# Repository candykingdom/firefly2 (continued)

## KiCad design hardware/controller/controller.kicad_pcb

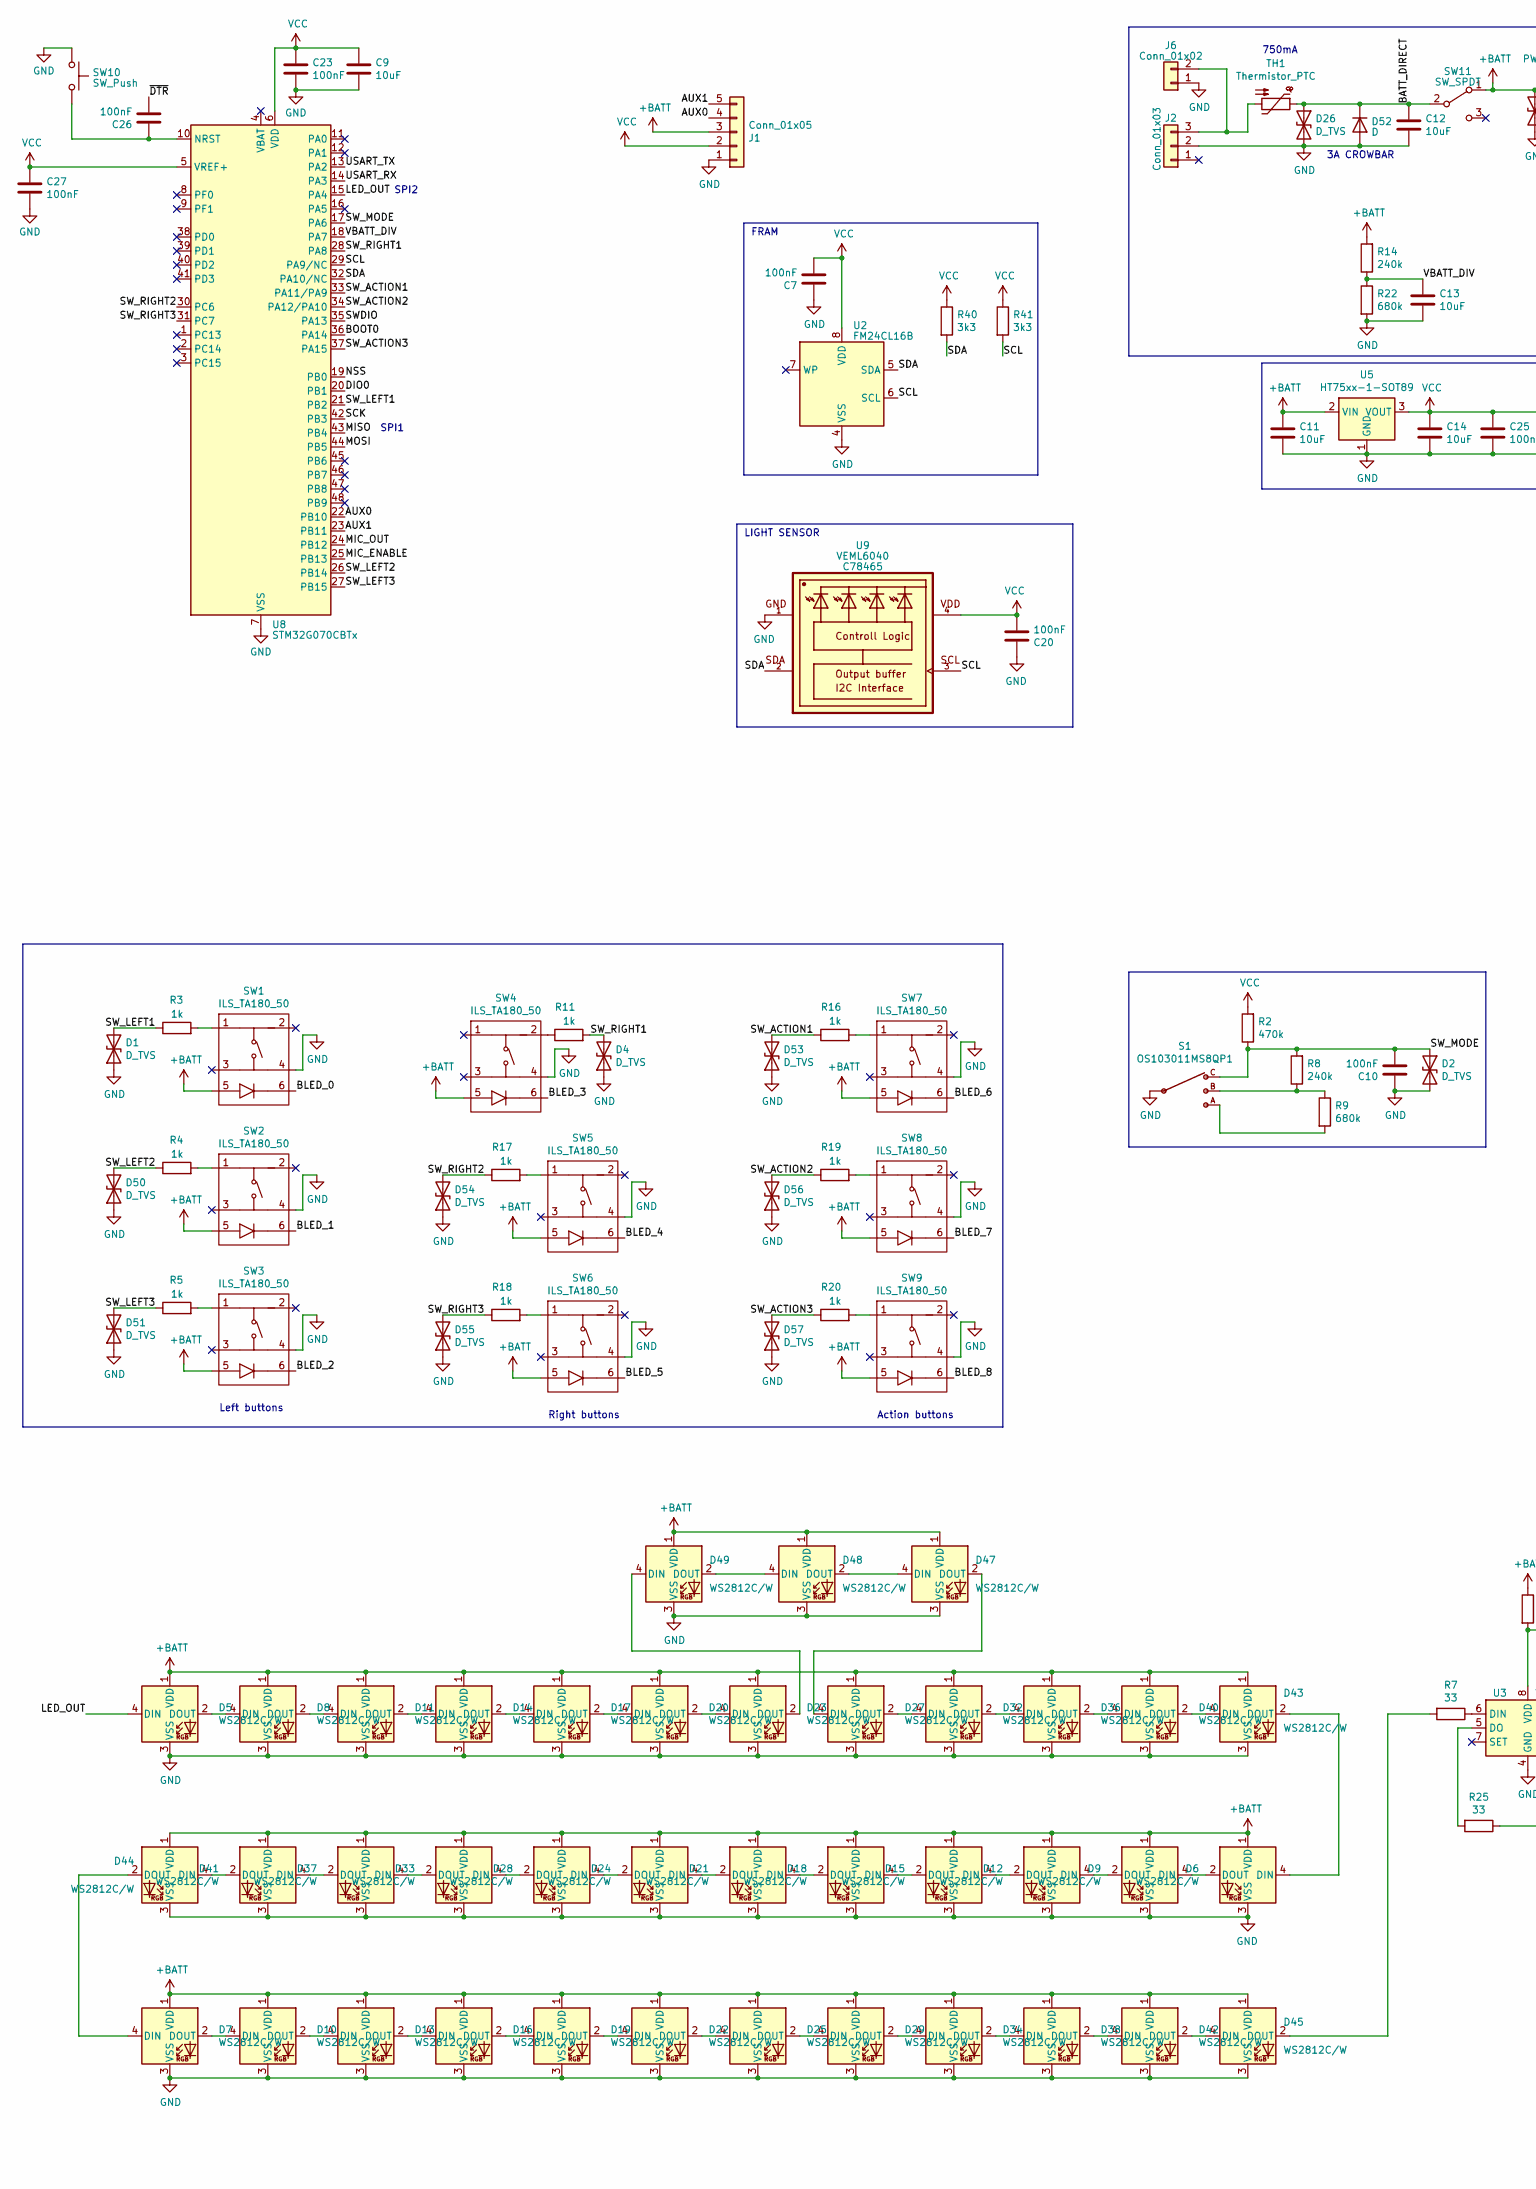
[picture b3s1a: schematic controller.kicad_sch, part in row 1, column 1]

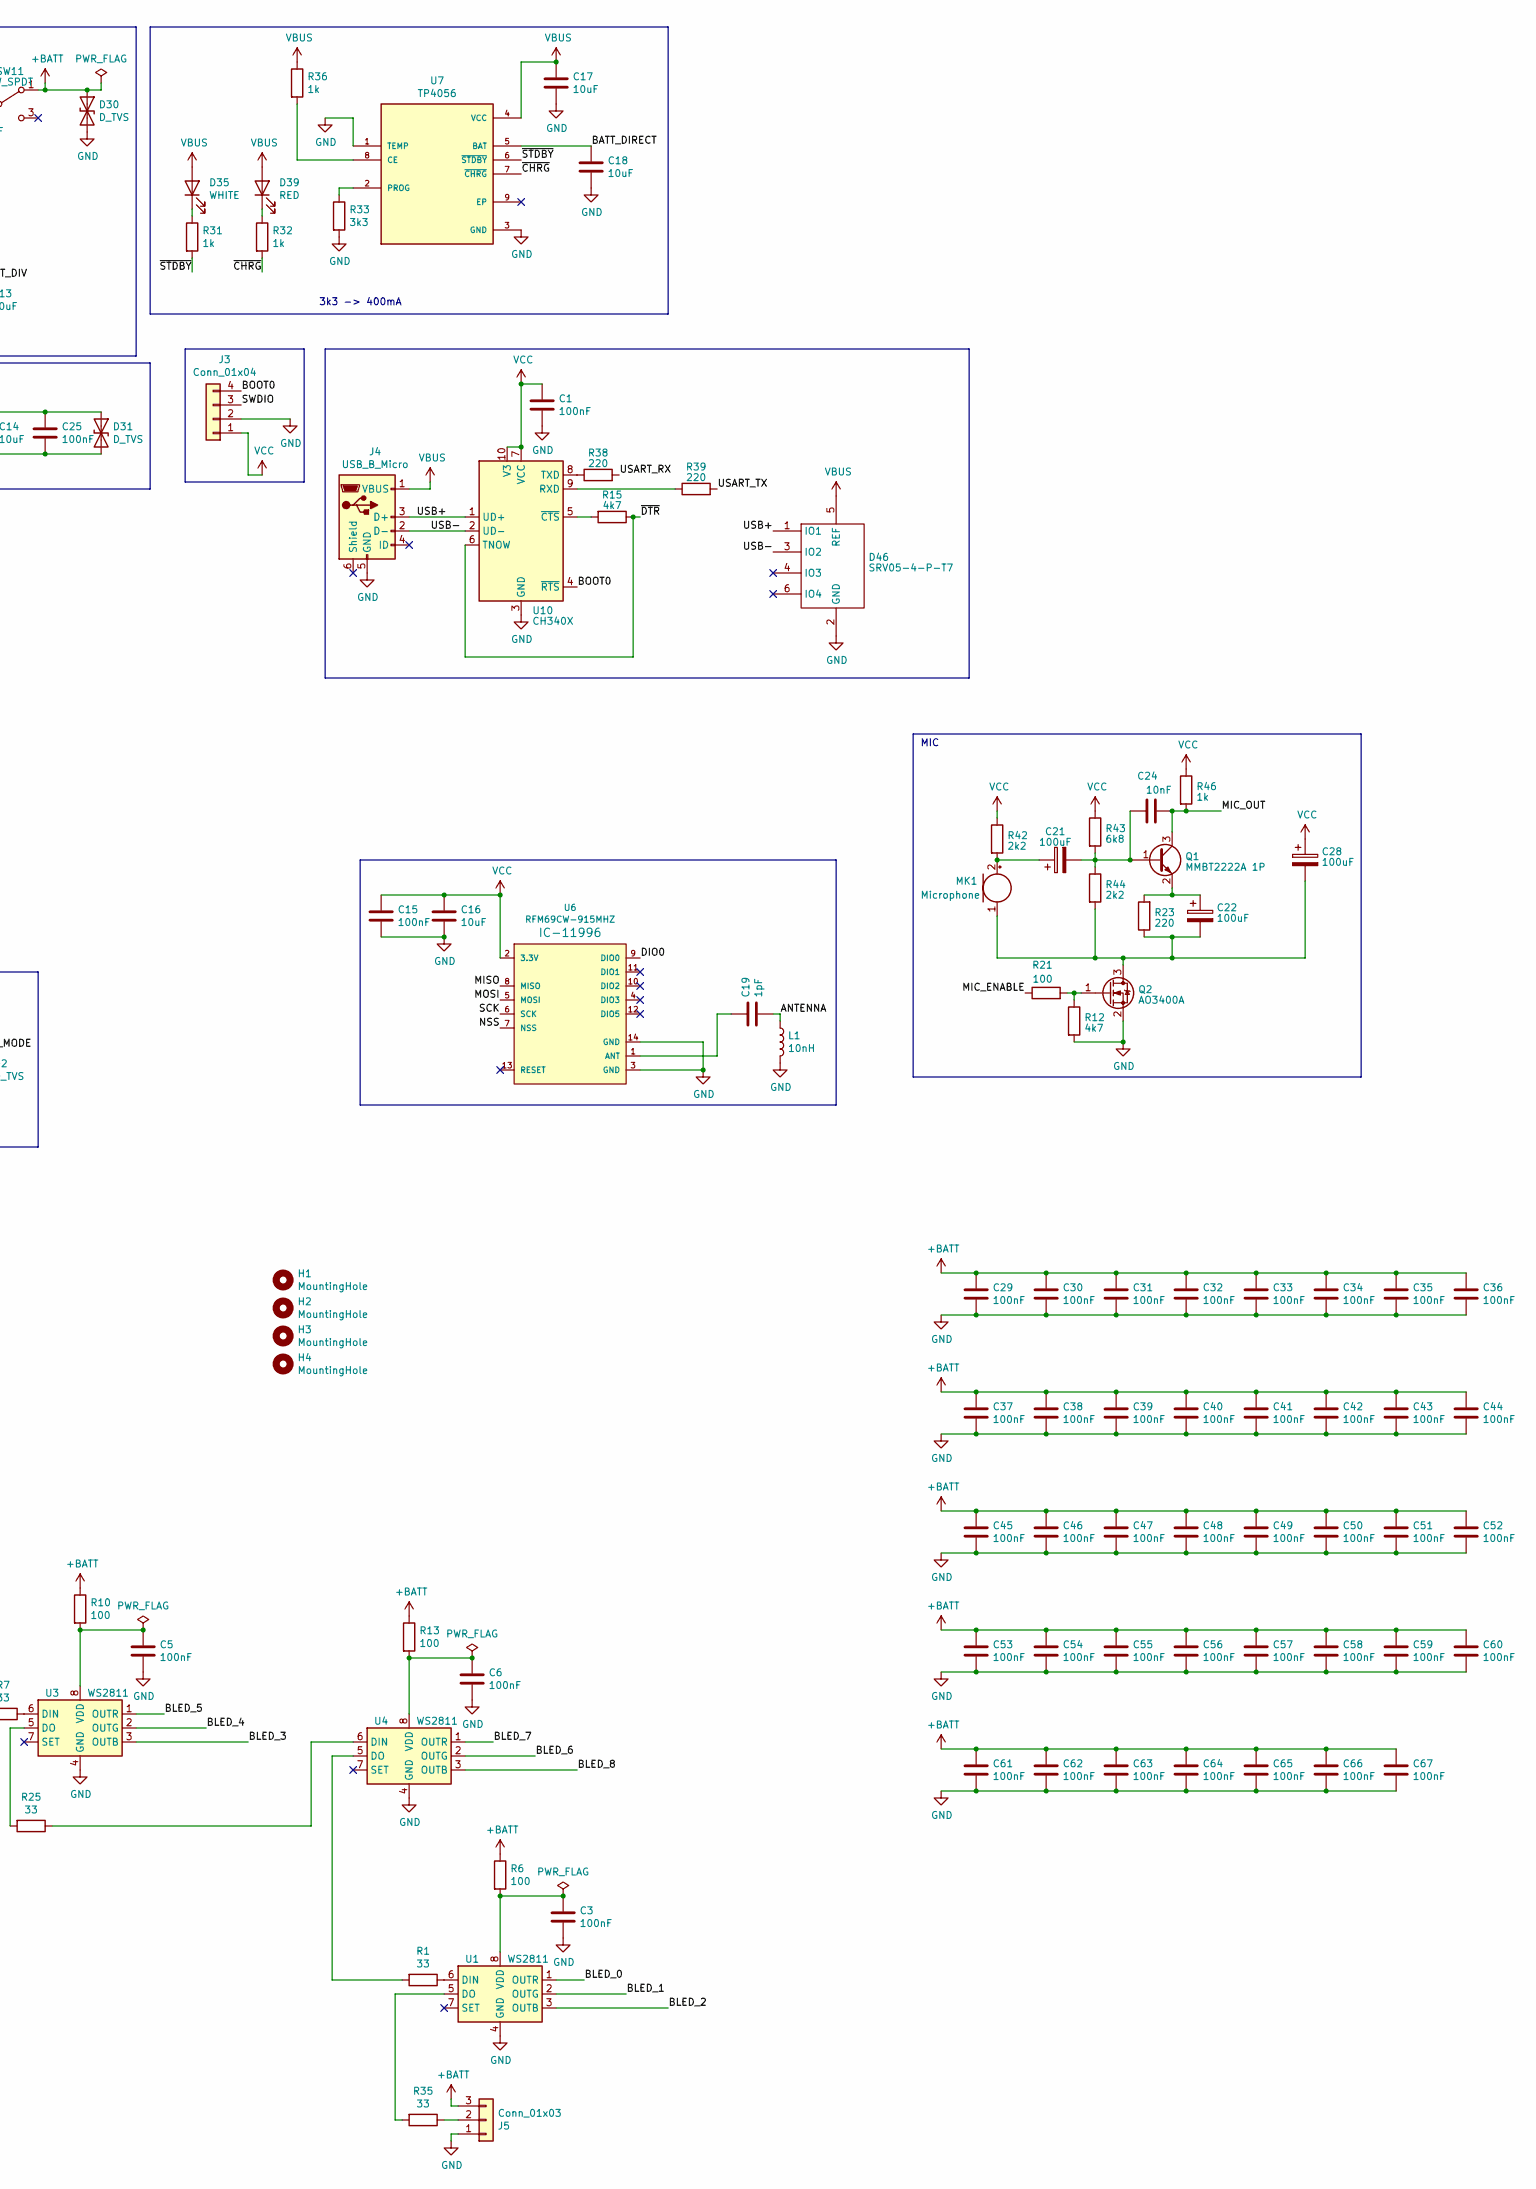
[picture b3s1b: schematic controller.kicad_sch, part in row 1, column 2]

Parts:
C1, C3, C5, C6, C7, C10, C15, C20, C23, C25, C26, C27, C29, C30, C31, C32, C33, C34, C35, C36, C37, C38, C39, C40, C41, C42, C43, C44, C45, C46, C47, C48, C49, C50, C51, C52, C53, C54, C55, C56, C57, C58, C59, C60, C61, C62, C63, C64, C65, C66, C67: 100nF; C_0402_1005Metric_Pad0.74x0.62mm_HandSolder; LCSC C307331
C9, C11, C12, C13, C14, C16, C17, C18: 10uF; C_0603_1608Metric; LCSC C96446
C19: 1pF; C_0402_1005Metric_Pad0.74x0.62mm_HandSolder; LCSC C1550
C21, C22, C28: 100uF; CP_Elec_6.3x5.4; LCSC C2887276
C24: 10nF; C_0603_1608Metric_Pad1.08x0.95mm_HandSolder; LCSC C85973
D1, D2, D4, D26, D30, D31, D50, D51, D53, D54, D55, D56, D57: D_TVS; D_SOD-123F; LCSC C2990473
D5, D6, D7, D8, D9, D10, D11, D12, D13, D14, D15, D16, D17, D18, D19, D20, D21, D22, D23, D24, D25, D27, D28, D29, D32, D33, D34, D36, D37, D38, D40, D41, D42, D43, D44, D45, D47, D48, D49: WS2812C/W; LED_WS2812B_PLCC4_5.0x5.0mm_P3.2mm; LCSC C2761796
D35: WHITE; LED_0603_1608Metric; LCSC C2290
D39: RED; LED_0603_1608Metric; LCSC C2286
D46: SRV05-4-P-T7; SOT-23-6; LCSC C85364
D52: D; D_SMA; LCSC C8678
H1, H2, H3, H4: MountingHole; MountingHole_3.2mm_M3
J1: Conn_01x05; PinHeader_1x05_P2.54mm_Vertical
J2: Conn_01x03; PinHeader_1x03_P2.54mm_Horizontal
J3: Conn_01x04; PinHeader_1x04_P2.54mm_Vertical
J4: USB_B_Micro; FRAMATOME_10118194-0001LF_fixed_bridges; LCSC C132563
J5: Conn_01x03; PinHeader_1x03_P2.54mm_Vertical
J6: Conn_01x02; JST_Micro_1x02_P1.25mm_Horizontal
L1: 10nH; L_0402_1005Metric; LCSC C27147
MK1: Microphone; MIC_CMA-4544PF-W; MPN CMA-4544PF-W
Q1: MMBT2222A 1P; SOT-23; LCSC C8512
Q2: AO3400A; SOT-23; LCSC C20917
R1, R7, R25, R35: 33; R_0603_1608Metric; LCSC C23140
R2: 470k; R_0603_1608Metric; LCSC C23178
R3, R4, R5, R11, R16, R17, R18, R19, R20, R31, R32, R36, R46: 1k; R_0402_1005Metric; LCSC C11702
R6, R10, R13, R21: 100; R_0402_1005Metric; LCSC C25076
R8, R14: 240k; R_0603_1608Metric; LCSC C4197
R9, R22: 680k; R_0603_1608Metric; LCSC C25822
R12, R15: 4k7; R_0402_1005Metric; LCSC C25900
R23, R38, R39: 220; R_0402_1005Metric; LCSC C25091
R33, R40, R41: 3k3; R_0603_1608Metric; LCSC C22978
R42, R44: 2k2; R_0603_1608Metric_Pad0.98x0.95mm_HandSolder; LCSC C4190
R43: 6k8; R_0603_1608Metric_Pad0.98x0.95mm_HandSolder; LCSC C23212
S1: OS103011MS8QP1; OS102011MS8QP1; MPN OS103011MS8QP1; DIGIKEY CKN9543-ND
SW1, SW2, SW3, SW4, SW5, SW6, SW7, SW8, SW9: ILS_TA180_50; SW_CK_TA; MPN ILS TA180 50
SW10: SW_Push; SW_TACTILE_5.1MM_TS-1187A-C-D-B; LCSC C318884
SW11: SW_SPDT; SW_SPDT_SK-12D02-G060; LCSC C2848884
TH1: Thermistor_PTC; Fuse_0805_2012Metric; LCSC C269105
U1, U3, U4: WS2811; SOP-8_3.9x4.9mm_P1.27mm; LCSC C114581
U2: FM24CL16B; SOIC-8_3.9x4.9mm_P1.27mm; LCSC C31082
U5: HT75xx-1-SOT89; SOT-89-3; LCSC C14289
U6: RFM69CW-915MHZ; RFM69CW-minimalpads
U7: TP4056; SOP127P600X175-9N; LCSC C382139
U8: STM32G070CBTx; LQFP-48_7x7mm_P0.5mm; LCSC C529338
U9: VEML6040; VISHAY_VEML6040_1.25X2X1; LCSC C78465
U10: CH340X; MSOP-10_3x3mm_P0.5mm; LCSC C3035748

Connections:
+BATT: C11.2, C29.1, C30.1, C31.1, C32.1, C33.1, C34.1, C35.1, C36.1, C37.1, C38.1, C39.1, C40.1, C41.1, C42.1, C43.1, C44.1, C45.1, C46.1, C47.1, C48.1, C49.1, C50.1, C51.1, C52.1, C53.1, C54.1, C55.1, C56.1, C57.1, C58.1, C59.1, C60.1, C61.1, C62.1, C63.1, C64.1, C65.1, C66.1, C67.1, D5.1 (VDD), D6.1 (VDD), D7.1 (VDD), D8.1 (VDD), D9.1 (VDD), D10.1 (VDD), D11.1 (VDD), D12.1 (VDD), D13.1 (VDD), D14.1 (VDD), D15.1 (VDD), D16.1 (VDD), D17.1 (VDD), D18.1 (VDD), D19.1 (VDD), D20.1 (VDD), D21.1 (VDD), D22.1 (VDD), D23.1 (VDD), D24.1 (VDD), D25.1 (VDD), D27.1 (VDD), D28.1 (VDD), D29.1 (VDD), D30.1 (A1), D32.1 (VDD), D33.1 (VDD), D34.1 (VDD), D36.1 (VDD), D37.1 (VDD), D38.1 (VDD), D40.1 (VDD), D41.1 (VDD), D42.1 (VDD), D43.1 (VDD), D44.1 (VDD), D45.1 (VDD), D47.1 (VDD), D48.1 (VDD), D49.1 (VDD), J1.3, J5.3, R6.1, R10.1, R13.1, R14.2, SW1.5, SW2.5, SW3.5, SW4.5, SW5.5, SW6.5, SW7.5, SW8.5, SW9.5, SW11.1 (A), U5.2 (VIN)
/ANTENNA: C19.2, L1.1
/AUX0: J1.4, U8.22 (PB10)
/AUX1: J1.5, U8.23 (PB11)
/BATT_DIRECT: C12.2, C18.2, D26.1 (A1), D52.1 (K), SW11.2 (B), TH1.1, U7.5 (BAT)
/BLED_0: SW1.6, U1.1 (OUTR)
/BLED_1: SW2.6, U1.2 (OUTG)
/BLED_2: SW3.6, U1.3 (OUTB)
/BLED_3: SW4.6, U3.3 (OUTB)
/BLED_4: SW5.6, U3.2 (OUTG)
/BLED_5: SW6.6, U3.1 (OUTR)
/BLED_6: SW7.6, U4.2 (OUTG)
/BLED_7: SW8.6, U4.1 (OUTR)
/BLED_8: SW9.6, U4.3 (OUTB)
/BOOT0: J3.4, U8.36 (PA14), U10.4 (~RTS)
/DIO0: U6.9 (DIO0), U8.20 (PB1)
/LED_OUT: D5.4 (DIN), U8.15 (PA4)
/MIC_ENABLE: R21.1, U8.25 (PB13)
/MIC_OUT: C24.2, Q1.3 (C), R46.2, U8.24 (PB12)
/MISO: U6.8 (MISO), U8.43 (PB4)
/MOSI: U6.5 (MOSI), U8.44 (PB5)
/NSS: U6.7 (NSS), U8.19 (PB0)
/SCK: U6.6 (SCK), U8.42 (PB3)
/SCL: R41.2, U2.6 (SCL), U8.29 (PA9/NC), U9.3
/SDA: R40.2, U2.5 (SDA), U8.32 (PA10/NC), U9.2
/SWDIO: J3.3, U8.35 (PA13)
/SW_ACTION1: D53.2 (A2), R16.1, U8.33 (PA11/PA9)
/SW_ACTION2: D56.2 (A2), R19.1, U8.34 (PA12/PA10)
/SW_ACTION3: D57.2 (A2), R20.1, U8.37 (PA15)
/SW_LEFT1: D1.2 (A2), R3.1, U8.21 (PB2)
/SW_LEFT2: D50.2 (A2), R4.1, U8.26 (PB14)
/SW_LEFT3: D51.2 (A2), R5.1, U8.27 (PB15)
/SW_MODE: C10.2, D2.1 (A1), R2.1, R8.2, S1.4, U8.17 (PA6)
/SW_RIGHT1: D4.2 (A2), R11.2, U8.28 (PA8)
/SW_RIGHT2: D54.2 (A2), R17.1, U8.30 (PC6)
/SW_RIGHT3: D55.2 (A2), R18.1, U8.31 (PC7)
/USART_RX: R38.2, U8.14 (PA3)
/USART_TX: R39.2, U8.13 (PA2)
/USB+: D46.1 (IO1), J4.3 (D+), U10.1 (UD+)
/USB-: D46.3 (IO2), J4.2 (D-), U10.2 (UD-)
/VBATT_DIV: C13.2, R14.1, R22.1, U8.18 (PA7)
/~CHRG: R32.2, U7.7 (~CHRG)
/~DTR: C26.2, R15.1, U10.6 (TNOW)
/~STDBY: R31.2, U7.6 (~STDBY)
GND: C1.2, C3.2, C5.2, C6.2, C7.1, C9.2, C10.1, C11.1, C12.1, C13.1, C14.1, C15.2, C16.1, C17.1, C18.1, C20.1, C23.2, C25.2, C27.2, C29.2, C30.2, C31.2, C32.2, C33.2, C34.2, C35.2, C36.2, C37.2, C38.2, C39.2, C40.2, C41.2, C42.2, C43.2, C44.2, C45.2, C46.2, C47.2, C48.2, C49.2, C50.2, C51.2, C52.2, C53.2, C54.2, C55.2, C56.2, C57.2, C58.2, C59.2, C60.2, C61.2, C62.2, C63.2, C64.2, C65.2, C66.2, C67.2, D1.1 (A1), D2.2 (A2), D4.1 (A1), D5.3 (VSS), D6.3 (VSS), D7.3 (VSS), D8.3 (VSS), D9.3 (VSS), D10.3 (VSS), D11.3 (VSS), D12.3 (VSS), D13.3 (VSS), D14.3 (VSS), D15.3 (VSS), D16.3 (VSS), D17.3 (VSS), D18.3 (VSS), D19.3 (VSS), D20.3 (VSS), D21.3 (VSS), D22.3 (VSS), D23.3 (VSS), D24.3 (VSS), D25.3 (VSS), D26.2 (A2), D27.3 (VSS), D28.3 (VSS), D29.3 (VSS), D30.2 (A2), D31.2 (A2), D32.3 (VSS), D33.3 (VSS), D34.3 (VSS), D36.3 (VSS), D37.3 (VSS), D38.3 (VSS), D40.3 (VSS), D41.3 (VSS), D42.3 (VSS), D43.3 (VSS), D44.3 (VSS), D45.3 (VSS), D46.2 (GND), D47.3 (VSS), D48.3 (VSS), D49.3 (VSS), D50.1 (A1), D51.1 (A1), D52.2 (A), D53.1 (A1), D54.1 (A1), D55.1 (A1), D56.1 (A1), D57.1 (A1), J1.1, J2.2, J3.2, J4.5 (GND), J5.1, J6.1, L1.2, Q2.2 (S), R12.2, R22.2, R33.2, S1.2, SW1.4, SW2.4, SW3.4, SW4.4, SW5.4, SW6.4, SW7.4, SW8.4, SW9.4, SW10.1, U1.4 (GND), U2.4 (VSS), U3.4 (GND), U4.4 (GND), U5.1 (GND), U6.3 (GND), U6.14 (GND), U7.1 (TEMP), U7.3 (GND), U8.7 (VSS), U9.1, U10.3 (GND)
unnamed: C6.1, R13.2, U4.8 (VDD)
unnamed: C5.1, R10.2, U3.8 (VDD)
unnamed: C3.1, R6.2, U1.8 (VDD)
unnamed: D5.2 (DOUT), D8.4 (DIN)
unnamed: D6.2 (DOUT), D9.4 (DIN)
unnamed: D7.2 (DOUT), D10.4 (DIN)
unnamed: D10.2 (DOUT), D13.4 (DIN)
unnamed: D8.2 (DOUT), D11.4 (DIN)
unnamed: D11.2 (DOUT), D14.4 (DIN)
unnamed: D9.2 (DOUT), D12.4 (DIN)
unnamed: D12.2 (DOUT), D15.4 (DIN)
unnamed: D13.2 (DOUT), D16.4 (DIN)
unnamed: D14.2 (DOUT), D17.4 (DIN)
unnamed: D15.2 (DOUT), D18.4 (DIN)
unnamed: D16.2 (DOUT), D19.4 (DIN)
unnamed: D17.2 (DOUT), D20.4 (DIN)
unnamed: D18.2 (DOUT), D21.4 (DIN)
unnamed: D19.2 (DOUT), D22.4 (DIN)
unnamed: D20.2 (DOUT), D23.4 (DIN)
unnamed: D21.2 (DOUT), D24.4 (DIN)
unnamed: D22.2 (DOUT), D25.4 (DIN)
unnamed: D23.2 (DOUT), D49.4 (DIN)
unnamed: D24.2 (DOUT), D28.4 (DIN)
unnamed: D25.2 (DOUT), D29.4 (DIN)
unnamed: D27.4 (DIN), D47.2 (DOUT)
unnamed: D27.2 (DOUT), D32.4 (DIN)
unnamed: D28.2 (DOUT), D33.4 (DIN)
unnamed: D29.2 (DOUT), D34.4 (DIN)
unnamed: D32.2 (DOUT), D36.4 (DIN)
unnamed: D33.2 (DOUT), D37.4 (DIN)
unnamed: D34.2 (DOUT), D38.4 (DIN)
unnamed: D35.1 (K), R31.1
unnamed: D36.2 (DOUT), D40.4 (DIN)
unnamed: D37.2 (DOUT), D41.4 (DIN)
unnamed: D38.2 (DOUT), D42.4 (DIN)
unnamed: D39.1 (K), R32.1
unnamed: D40.2 (DOUT), D43.4 (DIN)
unnamed: D41.2 (DOUT), D44.4 (DIN)
unnamed: D42.2 (DOUT), D45.4 (DIN)
unnamed: D6.4 (DIN), D43.2 (DOUT)
unnamed: D7.4 (DIN), D44.2 (DOUT)
unnamed: D45.2 (DOUT), R7.2
unnamed: D47.4 (DIN), D48.2 (DOUT)
unnamed: D48.4 (DIN), D49.2 (DOUT)
unnamed: J2.3, J6.2, TH1.2
unnamed: J5.2, R35.1
unnamed: C21.1, MK1.2 (+), R42.2
unnamed: C22.2, C28.2, MK1.1 (-), Q2.3 (D), R23.1, R44.2
unnamed: C21.2, C24.1, Q1.1 (B), R43.2, R44.1
unnamed: C22.1, Q1.2 (E), R23.2
unnamed: Q2.1 (G), R12.1, R21.2
unnamed: R3.2, SW1.1
unnamed: R4.2, SW2.1
unnamed: R5.2, SW3.1
unnamed: R8.1, R9.1, S1.3
unnamed: R9.2, S1.1
unnamed: R11.1, SW4.2
unnamed: R16.2, SW7.1
unnamed: R17.2, SW5.1
unnamed: R18.2, SW6.1
unnamed: R19.2, SW8.1
unnamed: R20.2, SW9.1
unnamed: R1.1, U1.6 (DIN)
unnamed: R35.2, U1.5 (DO)
unnamed: R7.1, U3.6 (DIN)
unnamed: R25.2, U3.5 (DO)
unnamed: R25.1, U4.6 (DIN)
unnamed: R1.2, U4.5 (DO)
unnamed: C19.1, U6.1 (ANT)
unnamed: R36.2, U7.8 (CE)
unnamed: R33.1, U7.2 (PROG)
unnamed: C26.1, SW10.2, U8.10 (NRST)
unnamed: R39.1, U10.9 (RXD)
unnamed: R38.1, U10.8 (TXD)
unnamed: R15.2, U10.5 (~CTS)
VBUS: C17.2, D35.2 (A), D39.2 (A), D46.5 (REF), J4.1 (VBUS), R36.1, U7.4 (VCC)
VCC: C1.1, C7.2, C9.1, C14.2, C15.1, C16.2, C20.2, C23.1, C25.1, C27.1, C28.1, D31.1 (A1), J1.2, J3.1, R2.2, R40.1, R41.1, R42.1, R43.1, R46.1, U2.8 (VDD), U5.3 (VOUT), U6.2 (3.3V), U8.5 (VREF+), U8.6 (VDD), U9.4, U10.7 (VCC), U10.10 (V3)

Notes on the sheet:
MIC
Right buttons
3k3 -> 400mA
SPI1
SPI2
Left buttons
Action buttons
3A CROWBAR
FRAM
LIGHT SENSOR
750mA

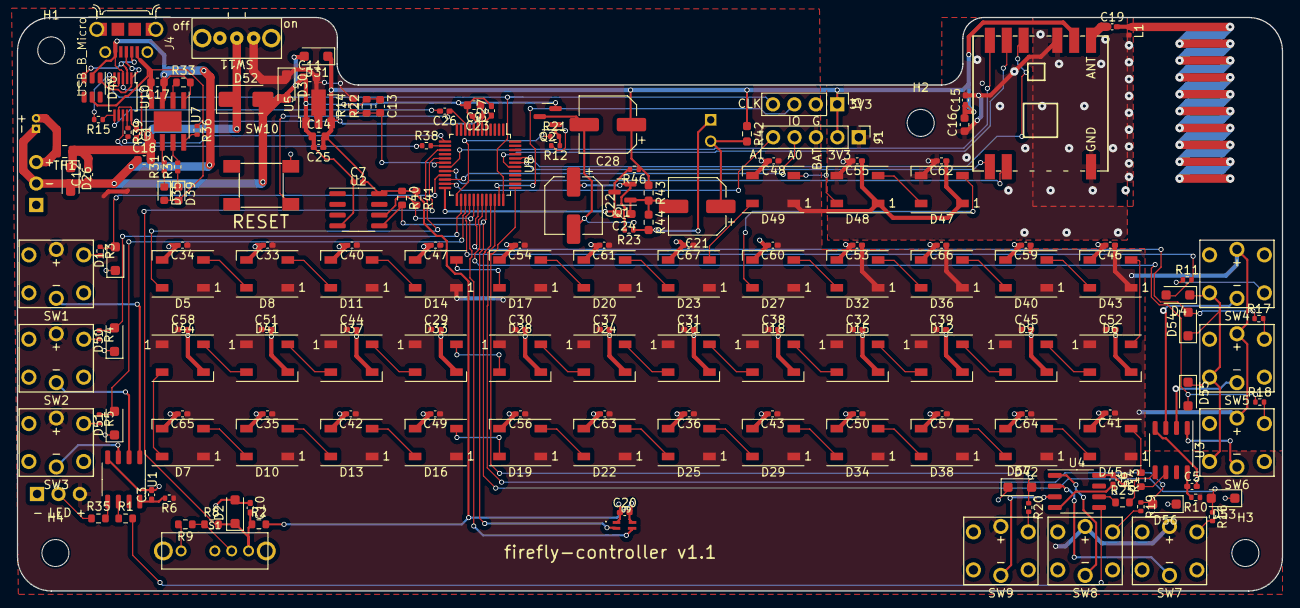
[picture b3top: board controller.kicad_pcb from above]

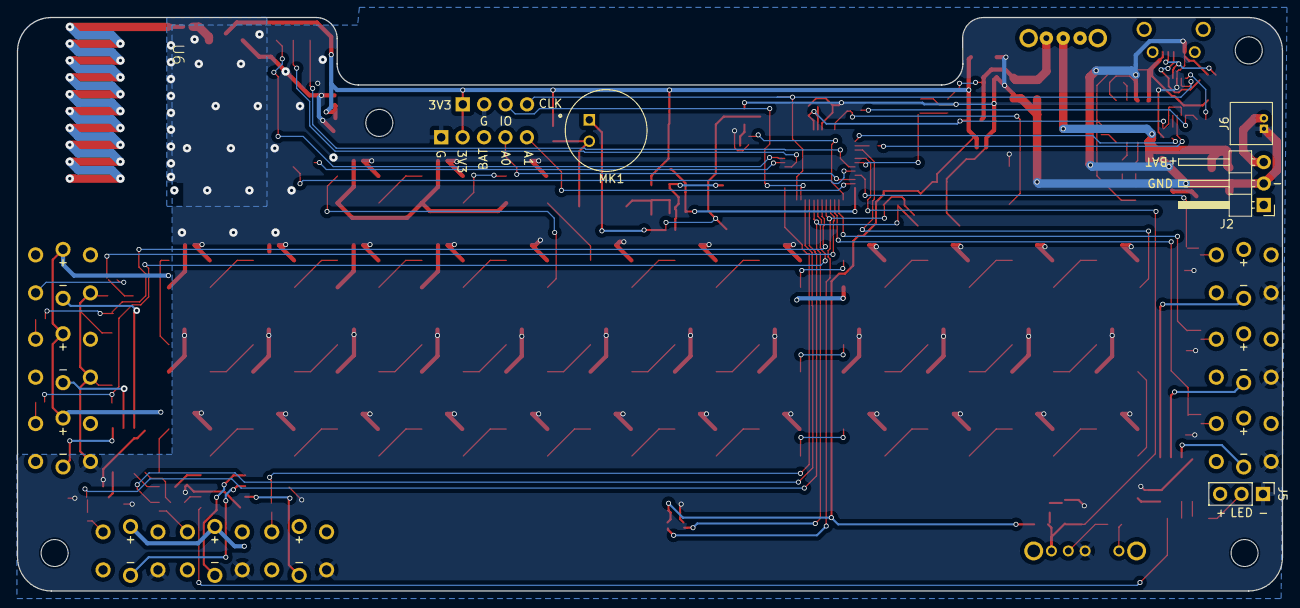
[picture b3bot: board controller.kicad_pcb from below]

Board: 2 copper layers, 150.0 x 68.0 mm, 194 parts (4 on the bottom side), 122 nets.

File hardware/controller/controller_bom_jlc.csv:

"Comment","Designator","Footprint","LCSC Part #"
"100nF","C1,C3,C5,C6,C7,C10,C15,C20,C23,C25,C26,C27,C29,C30,C31,C32,C33,C34,C35,C36,C37,C38,C39,C40,C41,C42,C43,C44,C45,C46,C47,C48,C49,C50,C51,C52,C53,C54,C55,C56,C57,C58,C59,C60,C61,C62,C63,C64,C65,C66,C67","C_0402_1005Metric_Pad0.74x0.62mm_HandSolder","C307331"
"10uF","C9,C11,C12,C13,C14,C16,C17,C18","C_0603_1608Metric","C96446"
"1pF","C19","C_0402_1005Metric_Pad0.74x0.62mm_HandSolder","C1550"
"100uF","C21,C22,C28","CP_Elec_6.3x5.4","C2887276"
"10nF","C24","C_0603_1608Metric_Pad1.08x0.95mm_HandSolder","C85973"
"D_TVS","D1,D2,D4,D26,D30,D31,D50,D51,D53,D54,D55,D56,D57","D_SOD-123F","C2990473"
"WS2812C/W","D5,D6,D7,D8,D9,D10,D11,D12,D13,D14,D15,D16,D17,D18,D19,D20,D21,D22,D23,D24,D25,D27,D28,D29,D32,D33,D34,D36,D37,D38,D40,D41,D42,D43,D44,D45,D47,D48,D49","LED_WS2812B_PLCC4_5.0x5.0mm_P3.2mm","C2761796"
"WHITE","D35","LED_0603_1608Metric","C2290"
"RED","D39","LED_0603_1608Metric","C2286"
"SRV05-4-P-T7","D46","SOT-23-6","C85364"
"D","D52","D_SMA","C8678"
"USB_B_Micro","J4","FRAMATOME_10118194-0001LF_fixed_bridges","C132563"
"10nH","L1","L_0402_1005Metric","C27147"
"MMBT2222A 1P","Q1","SOT-23","C8512"
"AO3400A","Q2","SOT-23","C20917"
"33","R1,R7,R25,R35","R_0603_1608Metric","C23140"
"470k","R2","R_0603_1608Metric","C23178"
"1k","R3,R4,R5,R11,R16,R17,R18,R19,R20,R31,R32,R36,R46","R_0402_1005Metric","C11702"
"100","R6,R10,R13,R21","R_0402_1005Metric","C25076"
"240k","R8,R14","R_0603_1608Metric","C4197"
"680k","R9,R22","R_0603_1608Metric","C25822"
"4k7","R12,R15","R_0402_1005Metric","C25900"
"220","R23,R38,R39","R_0402_1005Metric","C25091"
"3k3","R33,R40,R41","R_0603_1608Metric","C22978"
"2k2","R42,R44","R_0603_1608Metric_Pad0.98x0.95mm_HandSolder","C4190"
"6k8","R43","R_0603_1608Metric_Pad0.98x0.95mm_HandSolder","C23212"
"SW_Push","SW10","SW_TACTILE_5.1MM_TS-1187A-C-D-B","C318884"
"SW_SPDT","SW11","SW_SPDT_SK-12D02-G060","C2848884"
"Thermistor_PTC","TH1","Fuse_0805_2012Metric","C269105"
"WS2811","U1,U3,U4","SOP-8_3.9x4.9mm_P1.27mm","C114581"
"FM24CL16B","U2","SOIC-8_3.9x4.9mm_P1.27mm","C31082"
"HT75xx-1-SOT89","U5","SOT-89-3","C14289"
"TP4056","U7","SOP127P600X175-9N","C382139"
"STM32G070CBTx","U8","LQFP-48_7x7mm_P0.5mm","C529338"
"VEML6040","U9","VISHAY_VEML6040_1.25X2X1","C78465"
"CH340X","U10","MSOP-10_3x3mm_P0.5mm","C3035748"

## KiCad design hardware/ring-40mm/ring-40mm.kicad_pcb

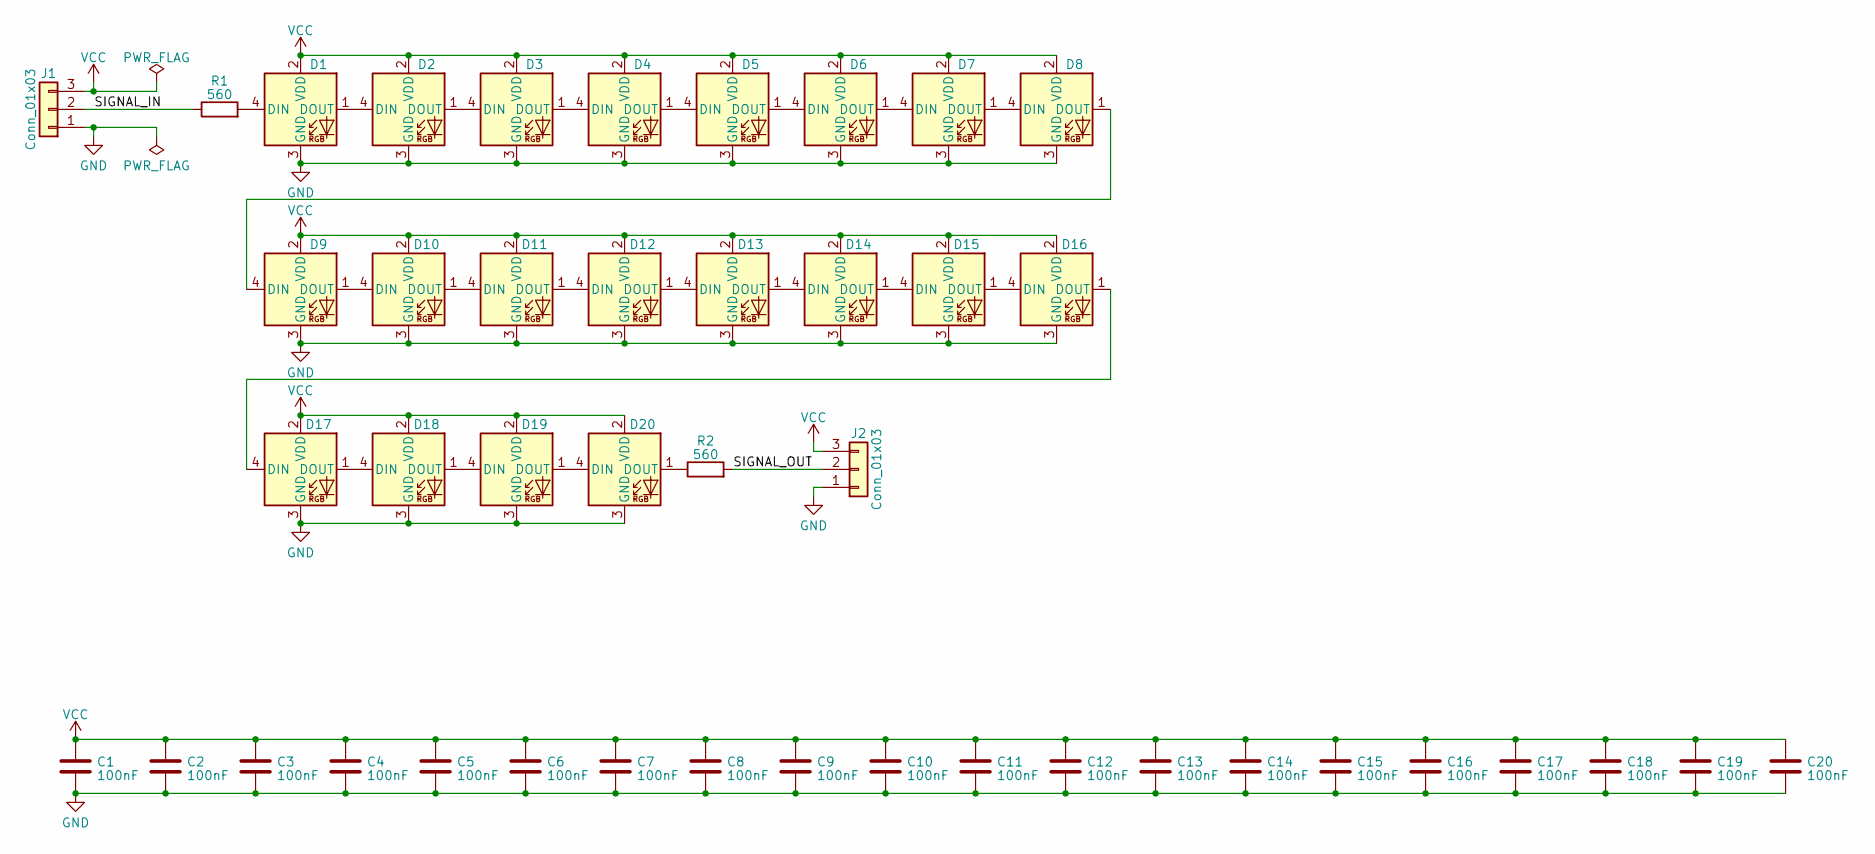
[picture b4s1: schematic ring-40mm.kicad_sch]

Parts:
C1, C2, C3, C4, C5, C6, C7, C8, C9, C10, C11, C12, C13, C14, C15, C16, C17, C18, C19, C20: 100nF; C_0402_1005Metric; LCSC C307331
D1, D2, D3, D4, D5, D6, D7, D8, D9, D10, D11, D12, D13, D14, D15, D16, D17, D18, D19, D20: XL-1010RGBC-WS2812B; XINGLIGHT-XL-1010RGBC-WS2812B; LCSC C5349953
J1, J2: Conn_01x03; PinHeader_1x03_P2.54mm_Vertical
R1, R2: 560; R_0603_1608Metric_Pad0.98x0.95mm_HandSolder; LCSC C23204

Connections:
/SIGNAL_IN: J1.2, R1.1
/SIGNAL_OUT: J2.2, R2.2
GND: C1.2, C2.2, C3.2, C4.2, C5.2, C6.2, C7.2, C8.2, C9.2, C10.2, C11.2, C12.2, C13.2, C14.2, C15.2, C16.2, C17.2, C18.2, C19.2, C20.2, D1.3 (GND), D2.3 (GND), D3.3 (GND), D4.3 (GND), D5.3 (GND), D6.3 (GND), D7.3 (GND), D8.3 (GND), D9.3 (GND), D10.3 (GND), D11.3 (GND), D12.3 (GND), D13.3 (GND), D14.3 (GND), D15.3 (GND), D16.3 (GND), D17.3 (GND), D18.3 (GND), D19.3 (GND), D20.3 (GND), J1.1, J2.1; also elsewhere on the board
unnamed: D1.4 (DIN), R1.2
unnamed: D1.1 (DOUT), D2.4 (DIN)
unnamed: D2.1 (DOUT), D3.4 (DIN)
unnamed: D3.1 (DOUT), D4.4 (DIN)
unnamed: D4.1 (DOUT), D5.4 (DIN)
unnamed: D5.1 (DOUT), D6.4 (DIN)
unnamed: D6.1 (DOUT), D7.4 (DIN)
unnamed: D7.1 (DOUT), D8.4 (DIN)
unnamed: D8.1 (DOUT), D9.4 (DIN)
unnamed: D9.1 (DOUT), D10.4 (DIN)
unnamed: D10.1 (DOUT), D11.4 (DIN)
unnamed: D11.1 (DOUT), D12.4 (DIN)
unnamed: D12.1 (DOUT), D13.4 (DIN)
unnamed: D13.1 (DOUT), D14.4 (DIN)
unnamed: D14.1 (DOUT), D15.4 (DIN)
unnamed: D15.1 (DOUT), D16.4 (DIN)
unnamed: D16.1 (DOUT), D17.4 (DIN)
unnamed: D17.1 (DOUT), D18.4 (DIN)
unnamed: D18.1 (DOUT), D19.4 (DIN)
unnamed: D19.1 (DOUT), D20.4 (DIN)
unnamed: D20.1 (DOUT), R2.1
VCC: C1.1, C2.1, C3.1, C4.1, C5.1, C6.1, C7.1, C8.1, C9.1, C10.1, C11.1, C12.1, C13.1, C14.1, C15.1, C16.1, C17.1, C18.1, C19.1, C20.1, D1.2 (VDD), D2.2 (VDD), D3.2 (VDD), D4.2 (VDD), D5.2 (VDD), D6.2 (VDD), D7.2 (VDD), D8.2 (VDD), D9.2 (VDD), D10.2 (VDD), D11.2 (VDD), D12.2 (VDD), D13.2 (VDD), D14.2 (VDD), D15.2 (VDD), D16.2 (VDD), D17.2 (VDD), D18.2 (VDD), D19.2 (VDD), D20.2 (VDD), J1.3, J2.3; also elsewhere on the board

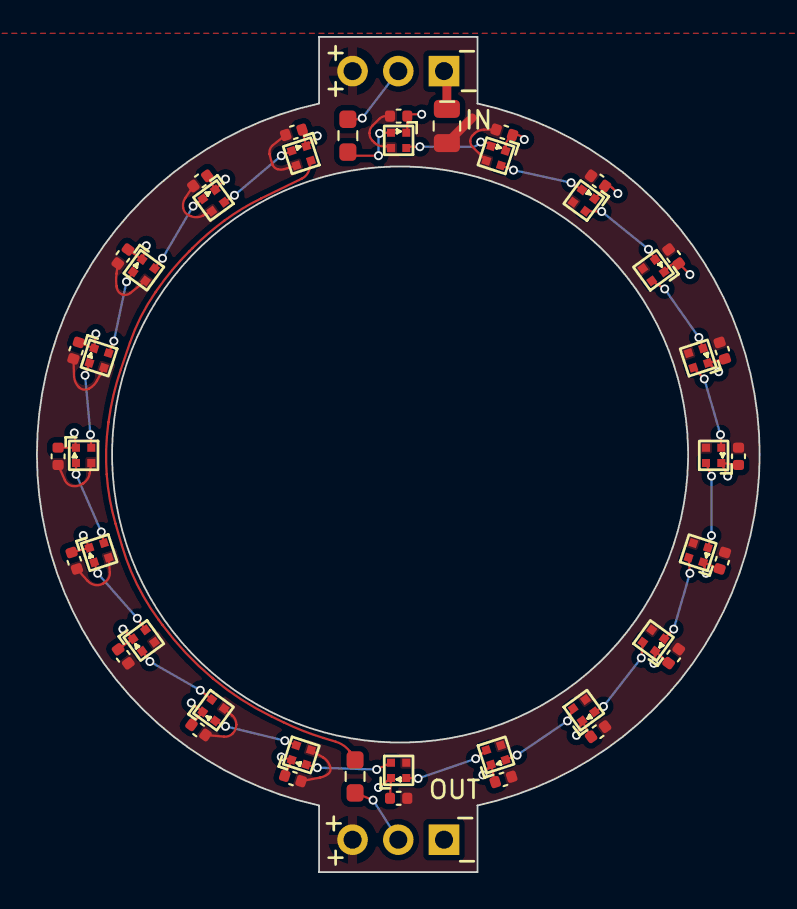
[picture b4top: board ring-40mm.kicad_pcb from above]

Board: 2 copper layers, 40.2 x 46.4 mm, 45 parts (0 on the bottom side), 25 nets.

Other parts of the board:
C21: 22uF; C_0805_2012Metric

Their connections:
GND: C21.2; also elsewhere on the board
VCC: C21.1; also elsewhere on the board

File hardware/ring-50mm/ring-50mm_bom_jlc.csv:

"Comment","Designator","Footprint","LCSC Part #"
"100nF","C1,C2,C3,C4,C5,C6,C7,C8,C9,C10,C11,C12,C13,C14,C15,C16,C17,C18,C19,C20,C21,C22,C23,C24","C_0402_1005Metric","C307331"
"22uF","C25","C_0805_2012Metric","C45783"
"XL-1010RGBC-WS2812B","D1,D2,D3,D4,D5,D6,D7,D8,D9,D10,D11,D12,D13,D14,D15,D16,D17,D18,D19,D20,D21,D22,D23,D24","XINGLIGHT-XL-1010RGBC-WS2812B","C5349953"
"560","R1,R2","R_0603_1608Metric_Pad0.98x0.95mm_HandSolder","C23204"

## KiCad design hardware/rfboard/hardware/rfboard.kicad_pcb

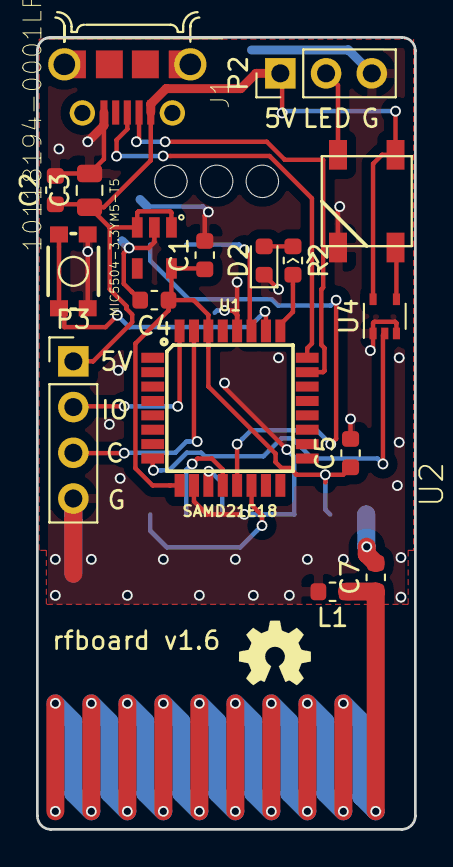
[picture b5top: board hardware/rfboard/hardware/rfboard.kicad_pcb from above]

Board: 2 copper layers, 21.0 x 44.0 mm, 19 parts (1 on the bottom side), 20 nets.

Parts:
C1, C2, C4, C5: 1uF; C_0603_1608Metric
C3: 10uF; C_0805_2012Metric
C7: 1pF; C_0603_1608Metric
D1: WS2812B
D2: LED; LED_0603_1608Metric
H3: STRAIN_RELIEF; 3_pin_2.54mm_pitch_strain_relief
J1: 10118194-0001LF; FRAMATOME_10118194-0001LF_fixed_bridges
L1: 10nH; L_0603_1608Metric
P2: CONN_01X03; PinHeader_1x03_P2.54mm_Vertical
P3: CONN_01X04; PinHeader_1x04_P2.54mm_Vertical
R2: 1k; R_0603_1608Metric
S1: MOMENTARY-SWITCH-SPST-SMD-4.6X2.8MM; TACTILE_SWITCH_SMD_4.6X2.8MM
U1: SAMD21E18; TQFP32-08
U2: RFM69CW-915MHZ; RFM69CW-minimalpads
U3: MIC5504-3.3YM5-T5; SOT23-5P95_280X145XL45X37N
U4: 74LVC1G125; SOT-353_SC-70-5

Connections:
+3V3: C1.1, C4.1, C5.1, U1.9, U1.30, U2.2, U3.5
+5V: C2.1, C3.1, D1.1, J1.1, P2.1, P3.1, U3.1, U3.3, U4.5
ANTENNA: C7.1, L1.1
ARM_SWCLK: P3.3, U1.31
ARM_SWDIO: P3.2, U1.32
GND: C1.2, C2.2, C3.2, C4.2, C5.2, D1.3, D2.1, J1.5, L1.2, P2.3, P3.4, S1.1, S1.2, U1.10, U1.28, U2.3, U2.14, U3.2, U4.1, U4.3
LED_EXTERNAL: D1.2, P2.2
LED_INTERNAL: U1.8, U4.2
unnamed: C7.2, U2.1
unnamed: D1.4, U4.4
unnamed: D2.2, R2.1
RADIO_DIO0: U1.27, U2.9
RADIO_MISO: U1.13, U2.8
RADIO_MOSI: U1.11, U2.5
RADIO_NSS: U1.14, U2.7
RADIO_SCK: U1.12, U2.6
RESET_SW: S1.3, S1.4, U1.26
SIMPLE_LED: R2.2, U1.25
USB_D+: J1.3, U1.24
USB_D-: J1.2, U1.23

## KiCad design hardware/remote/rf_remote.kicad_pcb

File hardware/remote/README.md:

# rf_remote
Remote control for light setup

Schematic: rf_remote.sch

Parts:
BT1: 3V battery; Keystone_3034_1x20mm-CoinCell
C1: 1.0UF-0603-16V-10%; C_0603
C2: 10UF-0603-6.3V-20%; C_0603
D1: LED; LED_0603
J1: 10118194-0001LF; FRAMATOME_10118194-0001LF
P1: CONN_01X04; 1X04
P2: CONN_01X01; 1X01
R1: 1k; R_0603_HandSoldering
S1, S2, S3, S4: MOMENTARY-SWITCH-6x6x4.5mm; 6x6x4.3mm button
U1: SAMD21E18; TQFP32-08
U2: RFM69CW-915MHZ; RFM69CW-XXXS2_

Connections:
+3V3: BT1.1 (+), C1.1, C2.1, U1.9 (VDDANA), U1.30 (VDDIN), U2.2 (3.3V)
ANTENNA: P2.1, U2.1 (ANT)
ARM_SWCLK: P1.3, U1.31 (PA30)
ARM_SWDIO: P1.2, U1.32 (PA31)
GND: BT1.2 (-), C1.2, C2.2, D1.1 (K), J1.5 (GND), P1.4, S1.1, S1.2, S2.1, S2.2, S3.1, S3.2, S4.1, S4.2, U1.10 (GND), U1.28 (GND), U2.3 (GND), U2.14 (GND)
unnamed: D1.2 (A), R1.1
RADIO_DIO0: U1.27 (PA28), U2.9 (DIO0)
RADIO_MISO: U1.13 (PA10), U2.8 (MISO)
RADIO_MOSI: U1.11 (PA08), U2.5 (MOSI)
RADIO_NSS: U1.14 (PA11), U2.7 (NSS)
RADIO_SCK: U1.12 (PA09), U2.6 (SCK)
SIMPLE_LED: R1.2, U1.25 (PA27)
SW1: S1.3, S1.4, U1.20 (PA19)
SW2: S2.3, S2.4, U1.19 (PA18)
SW3: S3.3, S3.4, U1.18 (PA17)
SW4: S4.3, S4.4, U1.17 (PA16)
USB_D+: J1.3 (D+), U1.24 (PA25)
USB_D-: J1.2 (D), U1.23 (PA24)

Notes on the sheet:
Firefly V2
2018-01-08
ARM Serial Wire Debug
Antenna
You can probably ditch the WS2812 that's on there, and of course the headers. A wire antenna should work - we can experiment with coiling it inside the enclosure (the Moteino folks use the same radio and have a variant with a PCB trace antenna - you could go for that too. RF design is a little tric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
processor, radio, and a couple of tactile switches. Using this as footprint for battery holder. Almost the same as the one recommended by polycase. http://www.keyelco.com/product.cfm/product_id/798 https://www.polycase.com/batt-hdr-fb?file=2d

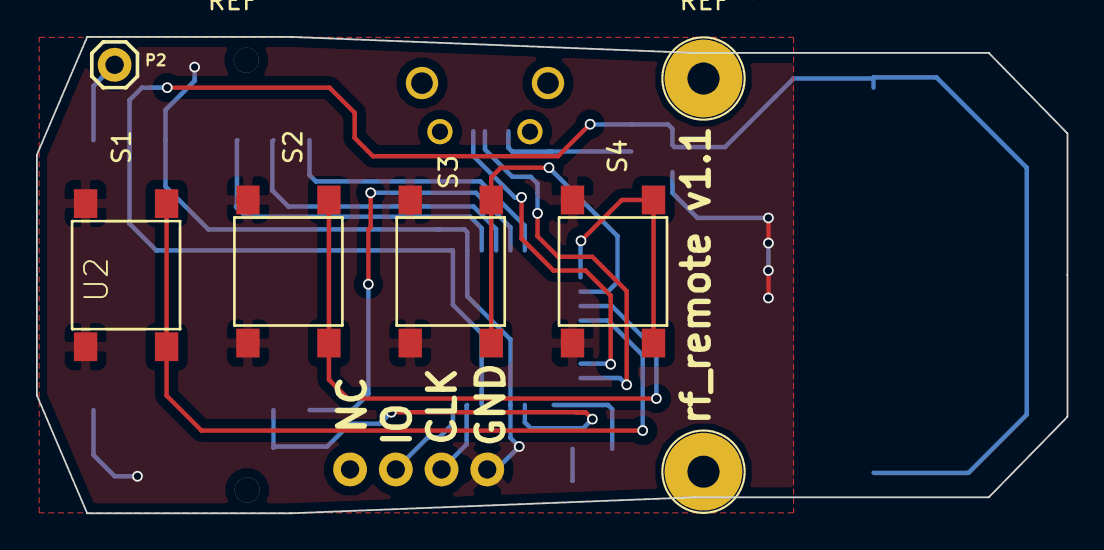
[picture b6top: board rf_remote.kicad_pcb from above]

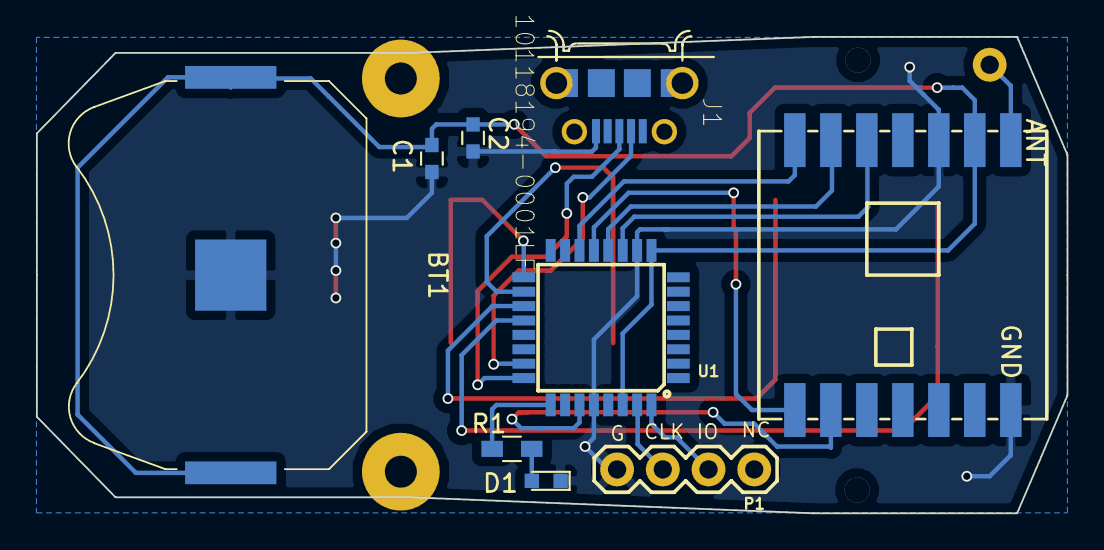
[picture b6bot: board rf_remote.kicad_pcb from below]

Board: 2 copper layers, 57.3 x 26.5 mm, 14 parts (9 on the bottom side), 18 nets.
